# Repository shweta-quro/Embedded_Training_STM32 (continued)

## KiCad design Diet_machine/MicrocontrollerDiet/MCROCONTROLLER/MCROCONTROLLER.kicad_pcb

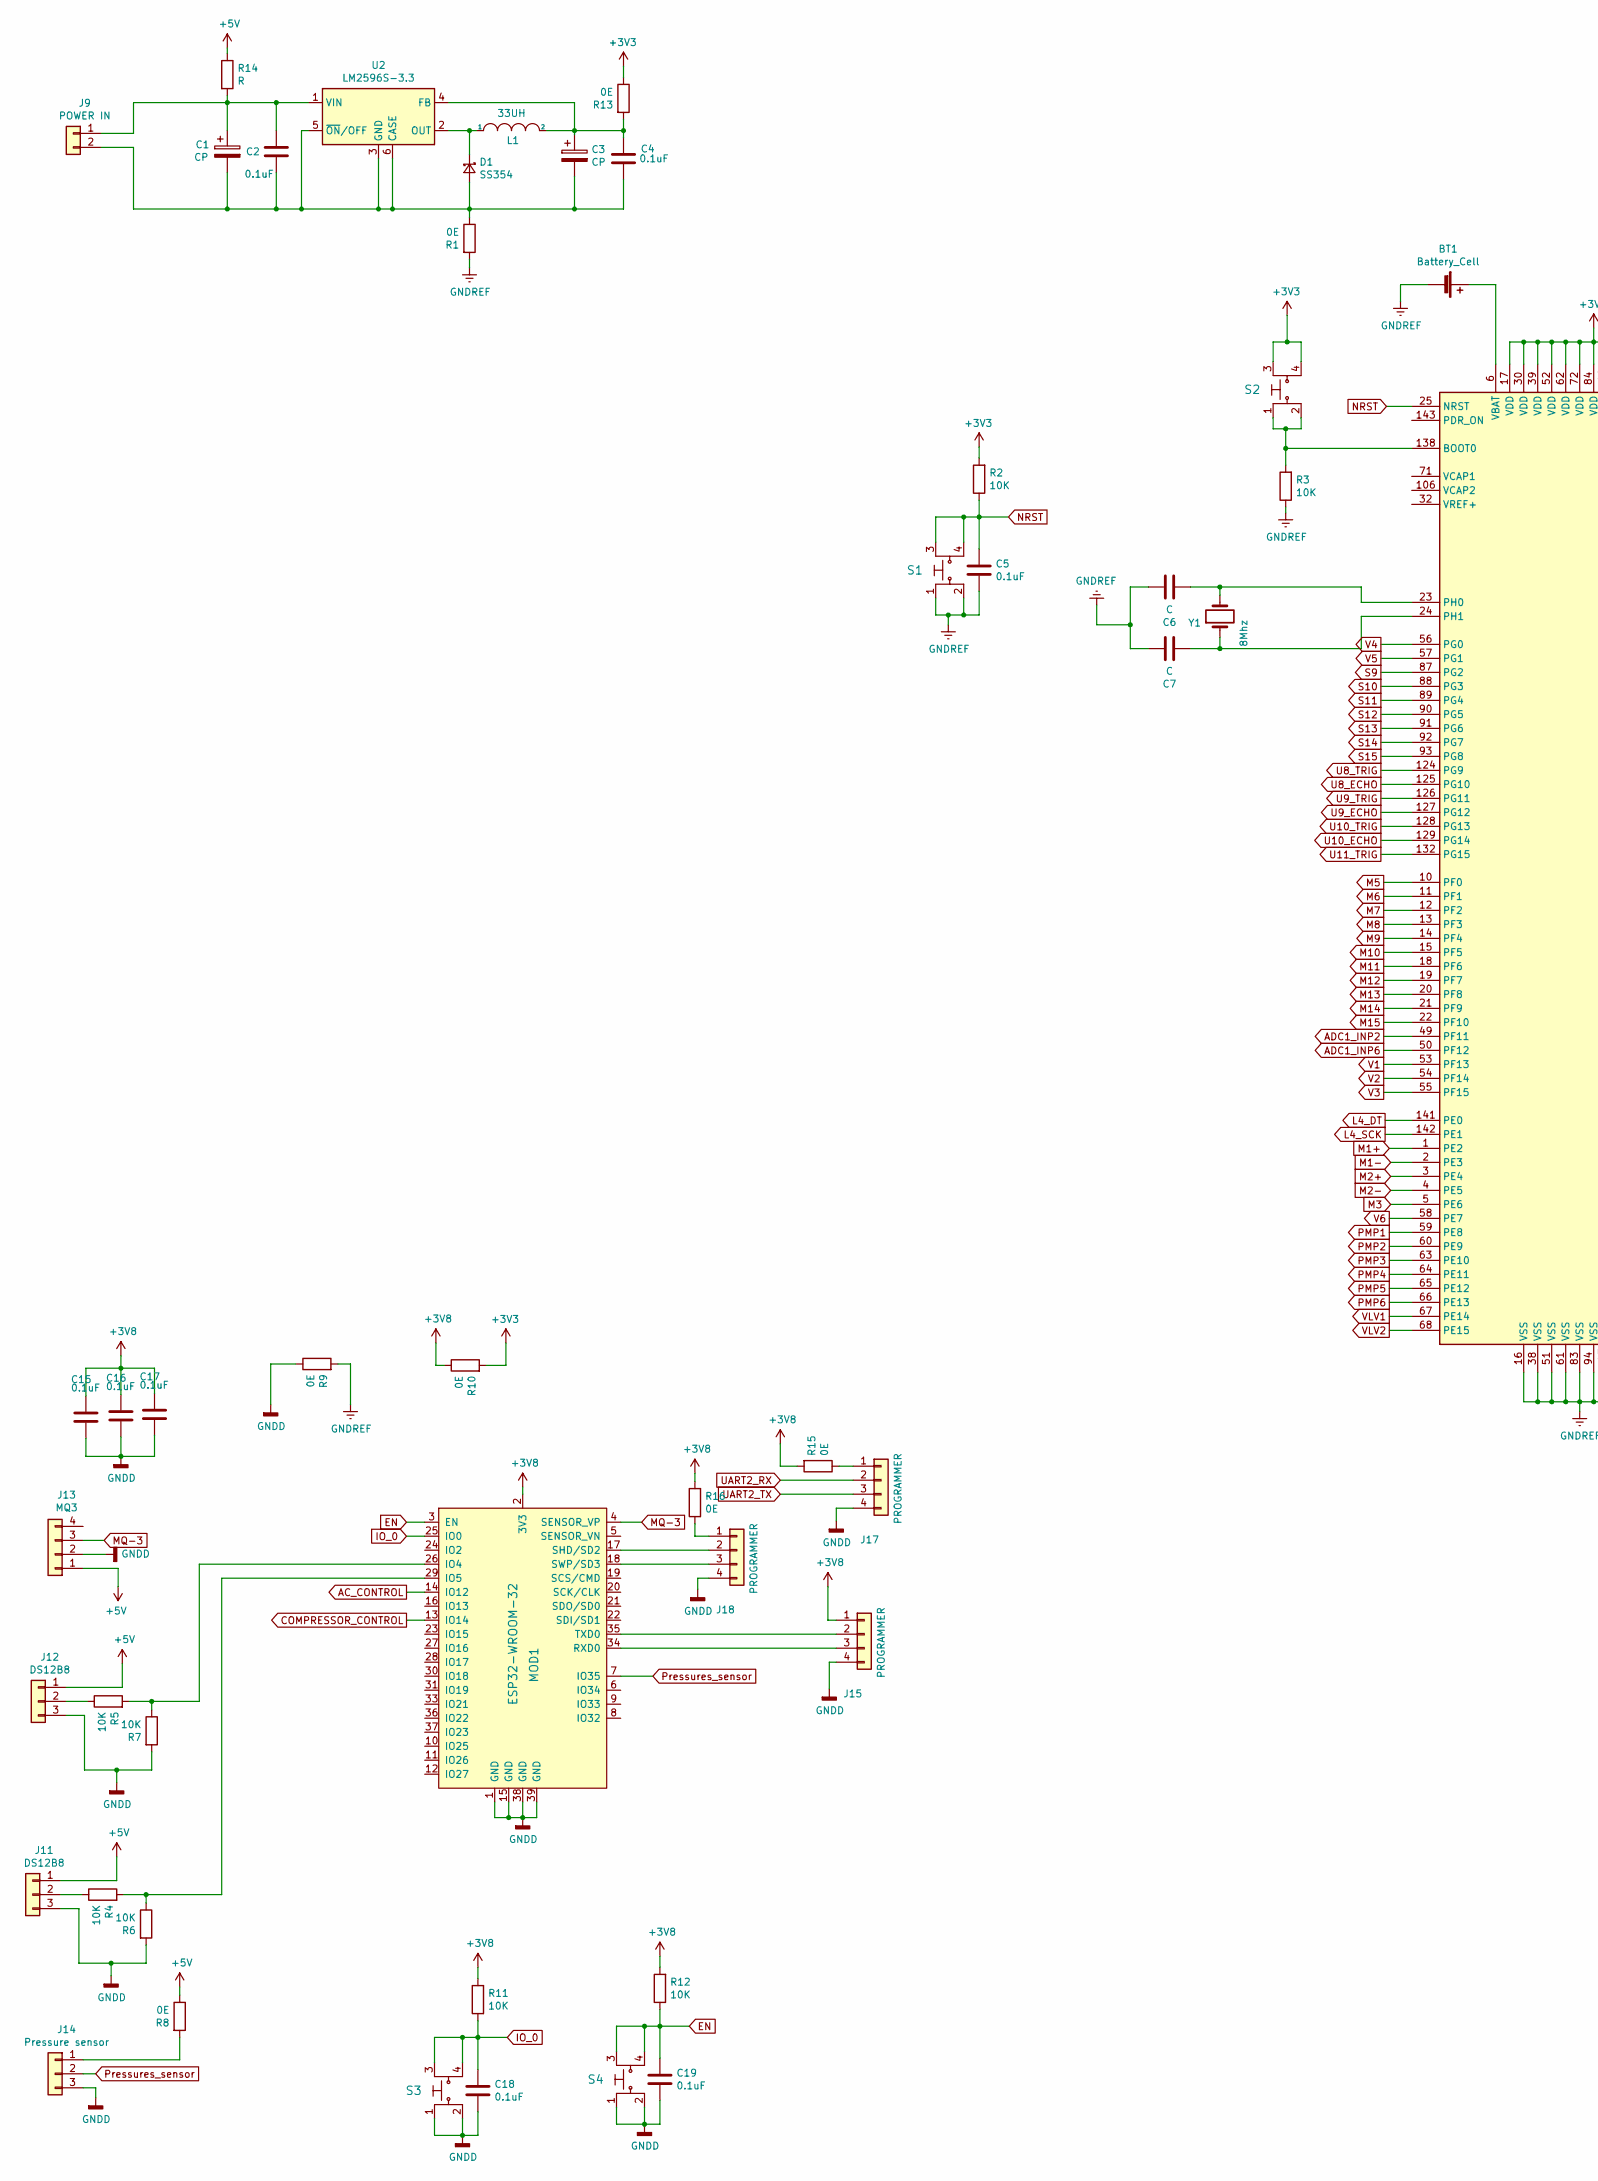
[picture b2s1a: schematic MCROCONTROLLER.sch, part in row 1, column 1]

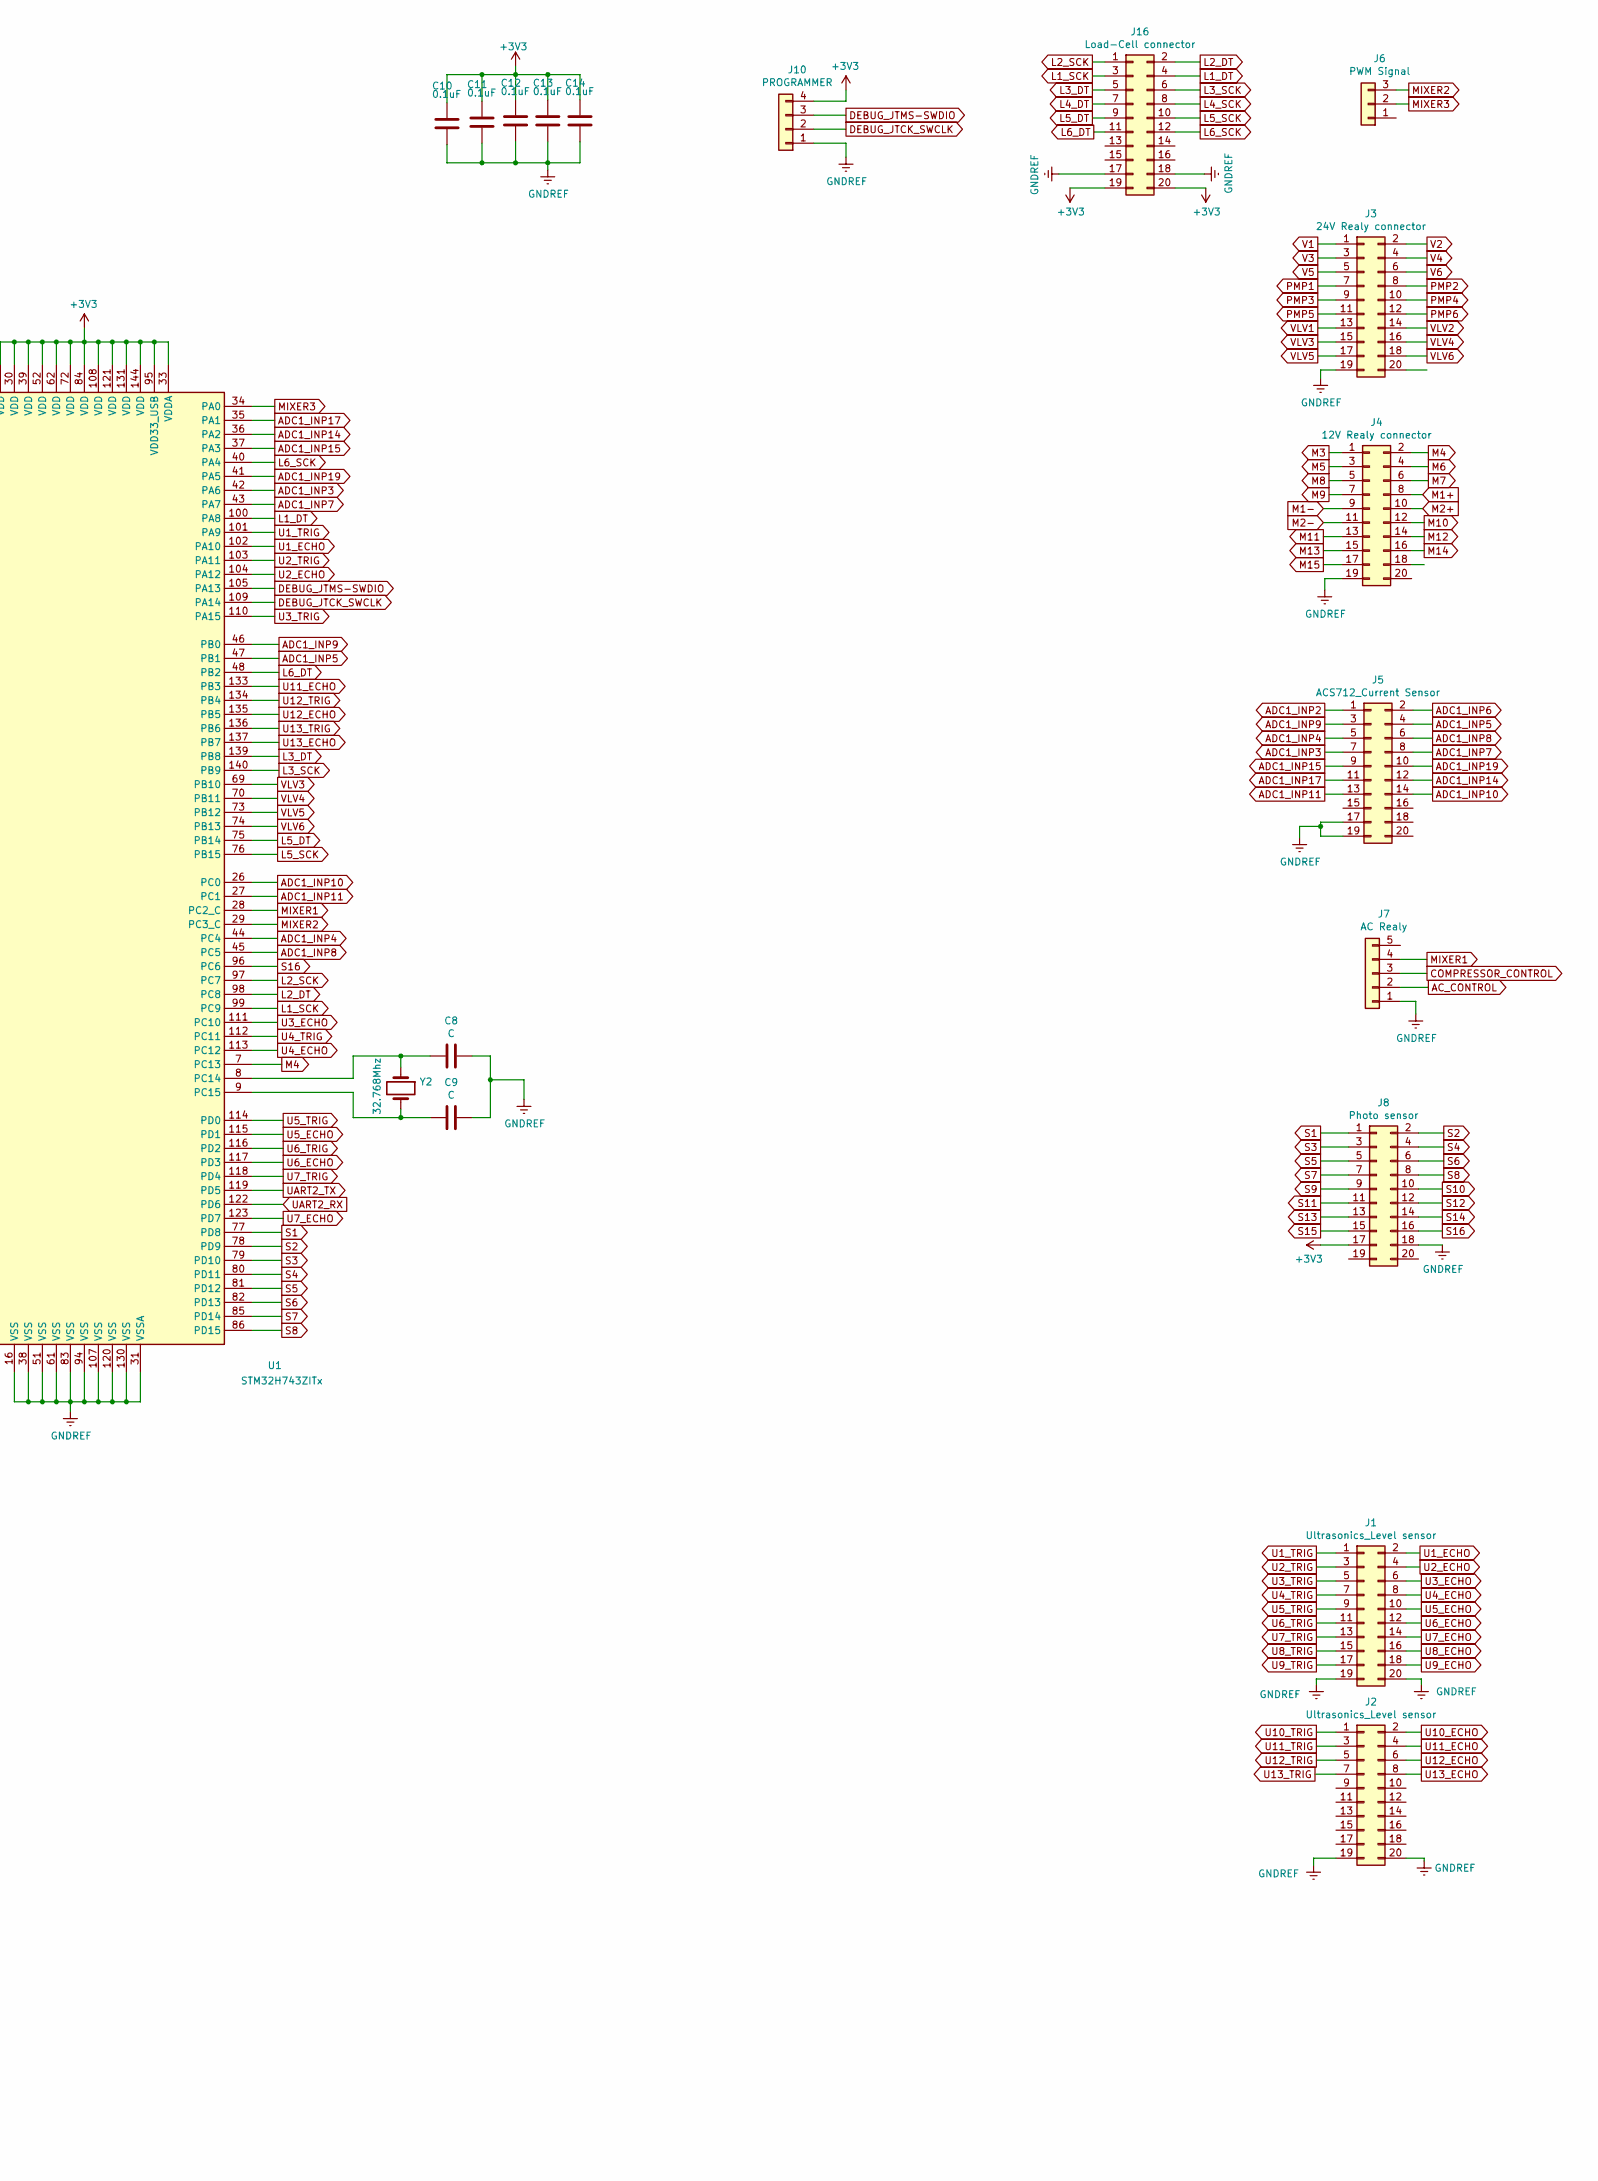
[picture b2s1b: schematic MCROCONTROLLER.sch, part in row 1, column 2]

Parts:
BT1: Battery_Cell; BatteryHolder_ComfortableElectronic_CH273-2450_1x2450
C1, C3: CP; CP_Radial_D8.0mm_P5.00mm
C2, C4, C10, C11, C12, C13, C14, C15, C16, C17: 0.1uF; C_0805_2012Metric_Pad1.18x1.45mm_HandSolder
C5, C18, C19: 0.1uF; C_0603_1608Metric
C6, C7, C8, C9: C; C_0603_1608Metric
D1: SS354; D_SS14
J1, J2: Ultrasonics_Level sensor; IDC-Header_2x10_P2.54mm_Vertical
J3: 24V Realy connector; IDC-Header_2x10_P2.54mm_Vertical
J4: 12V Realy connector; IDC-Header_2x10_P2.54mm_Vertical
J5: ACS712_Current Sensor; IDC-Header_2x10_P2.54mm_Vertical
J6: PWM Signal; PhoenixContact_MCV_1,5_3-G-5.08_1x03_P5.08mm_Vertical
J7: AC Realy; PhoenixContact_MCV_1,5_5-G-5.08_1x05_P5.08mm_Vertical
J8: Photo sensor; IDC-Header_2x10_P2.54mm_Vertical
J9: POWER IN; PhoenixContact_MCV_1,5_2-GF-5.08_1x02_P5.08mm_Vertical_Thre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
J10, J17, J18: PROGRAMMER; PinSocket_1x04_P2.54mm_Vertical
J11, J12: DS12B8; Molex_KK-254_AE-6410-03A_1x03_P2.54mm_Vertical
J13: MQ3; Molex_KK-254_AE-6410-04A_1x04_P2.54mm_Vertical
J14: Pressure sensor; Molex_KK-254_AE-6410-03A_1x03_P2.54mm_Vertical
J15: PROGRAMMER; PinSocket_2x02_P2.54mm_Vertical
J16: Load-Cell connector; IDC-Header_2x10_P2.54mm_Vertical
L1: 33UH; L_SMD1
MOD1: ESP32-WROOM-32; ESP32-WROOM-32D; MPN ESP32-WROOM-32; Digi-Key_PN 1904-1010-1-ND
R1, R9, R10, R13, R15, R16: 0E; R_1206_3216Metric
R2, R3, R4, R5, R6, R7, R11, R12: 10K; R_0603_1608Metric
R8: 0E; R_0603_1608Metric
R14: R; R_Axial_DIN0411_L9.9mm_D3.6mm_P20.32mm_Horizontal
S1, S2, S3, S4: PTS645SM43SMTR92_LFS; Switch_Tactile_THT_6x6mm; MPN PTS645SM43SMTR92 LFS; Digi-Key_PN CKN9112CT-ND
U1: STM32H743ZITx; LQFP-144_20x20mm_P0.5mm
U2: LM2596S-3.3; TO-263-5_TabPin3
Y1: 8Mhz; Crystal_HC49-4H_Vertical
Y2: 32.768Mhz; Crystal_Round_D1.5mm_Vertical

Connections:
+3V3: C10.1, C11.1, C12.1, C13.1, C14.1, J8.17, J10.4, J16.19, J16.20, R2.2, R10.2, R13.1, S2.3, S2.4, U1.17 (VDD), U1.30 (VDD), U1.33 (VDDA), U1.39 (VDD), U1.52 (VDD), U1.62 (VDD), U1.72 (VDD), U1.84 (VDD), U1.95 (VDD33_USB), U1.108 (VDD), U1.121 (VDD), U1.131 (VDD), U1.144 (VDD)
+3V8: C15.1, C16.1, C17.1, J15.1, MOD1.2 (3V3), R10.1, R11.2, R12.2, R15.2, R16.2
+5V: J11.1, J12.1, J13.1, R8.1, R14.1
AC_CONTROL: J7.2, MOD1.14 (IO12)
ADC1_INP2: J5.1, U1.49 (PF11)
ADC1_INP3: J5.7, U1.42 (PA6)
ADC1_INP4: J5.5, U1.44 (PC4)
ADC1_INP5: J5.4, U1.47 (PB1)
ADC1_INP6: J5.2, U1.50 (PF12)
ADC1_INP7: J5.8, U1.43 (PA7)
ADC1_INP8: J5.6, U1.45 (PC5)
ADC1_INP9: J5.3, U1.46 (PB0)
ADC1_INP10: J5.14, U1.26 (PC0)
ADC1_INP11: J5.13, U1.27 (PC1)
ADC1_INP14: J5.12, U1.36 (PA2)
ADC1_INP15: J5.9, U1.37 (PA3)
ADC1_INP17: J5.11, U1.35 (PA1)
ADC1_INP19: J5.10, U1.41 (PA5)
COMPRESSOR_CONTROL: J7.3, MOD1.13 (IO14)
DEBUG_JTCK_SWCLK: J10.2, U1.109 (PA14)
DEBUG_JTMS-SWDIO: J10.3, U1.105 (PA13)
EN: C19.1, MOD1.3 (EN), R12.1, S4.3, S4.4
GNDD: C15.2, C16.2, C17.2, C18.2, C19.2, J11.3, J12.3, J13.2, J14.3, J15.4, J17.4, J18.4, MOD1.1 (GND), MOD1.15 (GND), MOD1.38 (GND), MOD1.39 (GND), R6.2, R7.2, R9.1, S3.1, S3.2, S4.1, S4.2
GNDREF: BT1.2 (-), C5.2, C6.2, C7.2, C8.2, C9.2, C10.2, C11.2, C12.2, C13.2, C14.2, J1.19, J1.20, J2.19, J2.20, J3.19, J4.19, J5.17, J5.19, J7.1, J8.18, J10.1, J16.17, J16.18, R1.2, R3.1, R9.2, S1.1, S1.2, U1.16 (VSS), U1.31 (VSSA), U1.38 (VSS), U1.51 (VSS), U1.61 (VSS), U1.83 (VSS), U1.94 (VSS), U1.107 (VSS), U1.120 (VSS), U1.130 (VSS)
IO_0: C18.1, MOD1.25 (IO0), R11.1, S3.3, S3.4
L1_DT: J16.4, U1.100 (PA8)
L1_SCK: J16.3, U1.99 (PC9)
L2_DT: J16.2, U1.98 (PC8)
L2_SCK: J16.1, U1.97 (PC7)
L3_DT: J16.5, U1.139 (PB8)
L3_SCK: J16.6, U1.140 (PB9)
L4_DT: J16.7, U1.141 (PE0)
L4_SCK: J16.8, U1.142 (PE1)
L5_DT: J16.9, U1.75 (PB14)
L5_SCK: J16.10, U1.76 (PB15)
L6_DT: J16.11, U1.48 (PB2)
L6_SCK: J16.12, U1.40 (PA4)
M1+: J4.8, U1.1 (PE2)
M1-: J4.9, U1.2 (PE3)
M2+: J4.10, U1.3 (PE4)
M2-: J4.11, U1.4 (PE5)
M3: J4.1, U1.5 (PE6)
M4: J4.2, U1.7 (PC13)
M5: J4.3, U1.10 (PF0)
M6: J4.4, U1.11 (PF1)
M7: J4.6, U1.12 (PF2)
M8: J4.5, U1.13 (PF3)
M9: J4.7, U1.14 (PF4)
M10: J4.12, U1.15 (PF5)
M11: J4.13, U1.18 (PF6)
M12: J4.14, U1.19 (PF7)
M13: J4.15, U1.20 (PF8)
M14: J4.16, U1.21 (PF9)
M15: J4.17, U1.22 (PF10)
MIXER1: J7.4, U1.28 (PC2_C)
MIXER2: J6.3, U1.29 (PC3_C)
MIXER3: J6.2, U1.34 (PA0)
MQ-3: J13.3, MOD1.4 (SENSOR_VP)
NRST: C5.1, R2.1, S1.3, S1.4, U1.25 (NRST)
unnamed: BT1.1 (+), U1.6 (VBAT)
unnamed: C1.1, C2.1, J9.1, R14.2, U2.1 (VIN)
unnamed: C1.2, C2.2, C3.2, C4.2, D1.1 (A), J9.2, R1.1, U2.3 (GND), U2.5 (~ON~/OFF), U2.6 (CASE)
unnamed: C3.1, C4.1, L1.2, R13.2, U2.4 (FB)
unnamed: C6.1, U1.23 (PH0), Y1.2
unnamed: C7.1, U1.24 (PH1), Y1.1
unnamed: C8.1, U1.8 (PC14), Y2.1
unnamed: C9.1, U1.9 (PC15), Y2.2
unnamed: D1.2 (K), L1.1, U2.2 (OUT)
unnamed: J11.2, R4.1
unnamed: J12.2, R5.1
unnamed: J14.1, R8.2
unnamed: J15.2, MOD1.35 (TXD0)
unnamed: J15.3, MOD1.34 (RXD0)
unnamed: J17.1, R15.1
unnamed: J18.1, R16.1
unnamed: J18.2, MOD1.17 (SHD/SD2)
unnamed: J18.3, MOD1.18 (SWP/SD3)
unnamed: MOD1.26 (IO4), R5.2, R7.1
unnamed: MOD1.29 (IO5), R4.2, R6.1
unnamed: R3.2, S2.1, S2.2, U1.138 (BOOT0)
PMP1: J3.7, U1.59 (PE8)
PMP2: J3.8, U1.60 (PE9)
PMP3: J3.9, U1.63 (PE10)
PMP4: J3.10, U1.64 (PE11)
PMP5: J3.11, U1.65 (PE12)
PMP6: J3.12, U1.66 (PE13)
Pressures_sensor: J14.2, MOD1.7 (IO35)
S1: J8.1, U1.77 (PD8)
S2: J8.2, U1.78 (PD9)
S3: J8.3, U1.79 (PD10)
S4: J8.4, U1.80 (PD11)
S5: J8.5, U1.81 (PD12)
S6: J8.6, U1.82 (PD13)
S7: J8.7, U1.85 (PD14)
S8: J8.8, U1.86 (PD15)
S9: J8.9, U1.87 (PG2)
S10: J8.10, U1.88 (PG3)
S11: J8.11, U1.89 (PG4)
S12: J8.12, U1.90 (PG5)
S13: J8.13, U1.91 (PG6)
S14: J8.14, U1.92 (PG7)
S15: J8.15, U1.93 (PG8)
S16: J8.16, U1.96 (PC6)
U1_ECHO: J1.2, U1.102 (PA10)
U1_TRIG: J1.1, U1.101 (PA9)
U2_ECHO: J1.4, U1.104 (PA12)
U2_TRIG: J1.3, U1.103 (PA11)
U3_ECHO: J1.6, U1.111 (PC10)
U3_TRIG: J1.5, U1.110 (PA15)
U4_ECHO: J1.8, U1.113 (PC12)
U4_TRIG: J1.7, U1.112 (PC11)
U5_ECHO: J1.10, U1.115 (PD1)
U5_TRIG: J1.9, U1.114 (PD0)
U6_ECHO: J1.12, U1.117 (PD3)
U6_TRIG: J1.11, U1.116 (PD2)
U7_ECHO: J1.14, U1.123 (PD7)
U7_TRIG: J1.13, U1.118 (PD4)
U8_ECHO: J1.16, U1.125 (PG10)
U8_TRIG: J1.15, U1.124 (PG9)
U9_ECHO: J1.18, U1.127 (PG12)
U9_TRIG: J1.17, U1.126 (PG11)
U10_ECHO: J2.2, U1.129 (PG14)
U10_TRIG: J2.1, U1.128 (PG13)
U11_ECHO: J2.4, U1.133 (PB3)
U11_TRIG: J2.3, U1.132 (PG15)
U12_ECHO: J2.6, U1.135 (PB5)
U12_TRIG: J2.5, U1.134 (PB4)
U13_ECHO: J2.8, U1.137 (PB7)
U13_TRIG: J2.7, U1.136 (PB6)
UART2_RX: J17.2, U1.122 (PD6)
UART2_TX: J17.3, U1.119 (PD5)
V1: J3.1, U1.53 (PF13)
V2: J3.2, U1.54 (PF14)
V3: J3.3, U1.55 (PF15)
V4: J3.4, U1.56 (PG0)
V5: J3.5, U1.57 (PG1)
V6: J3.6, U1.58 (PE7)
VLV1: J3.13, U1.67 (PE14)
VLV2: J3.14, U1.68 (PE15)
VLV3: J3.15, U1.69 (PB10)
VLV4: J3.16, U1.70 (PB11)
VLV5: J3.17, U1.73 (PB12)
VLV6: J3.18, U1.74 (PB13)

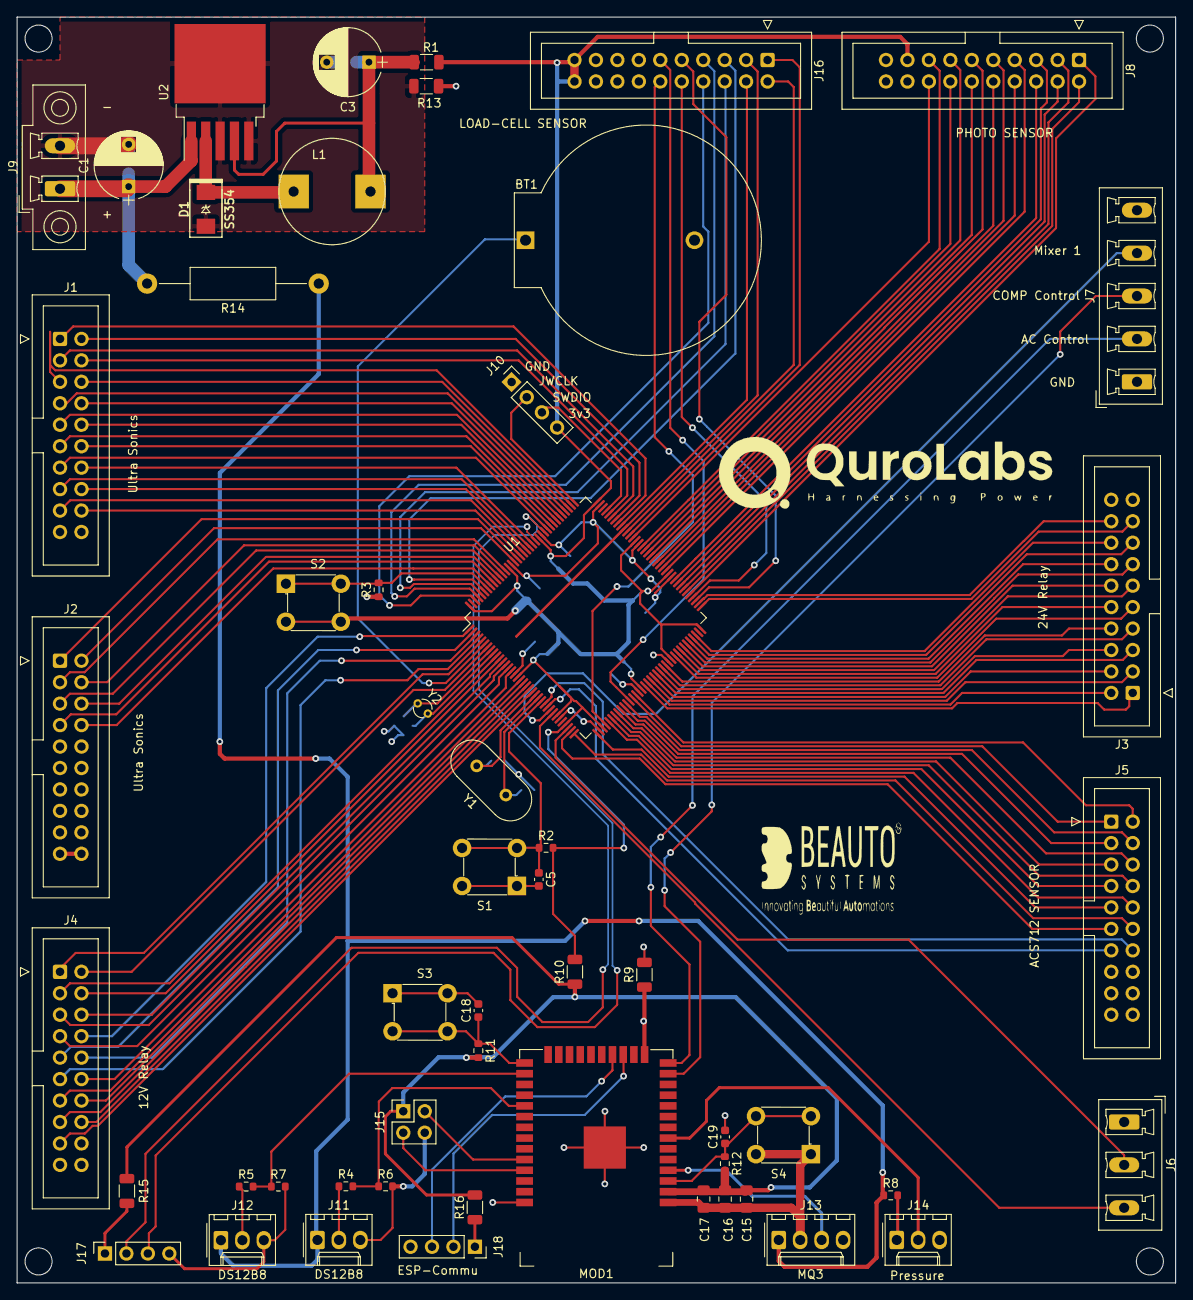
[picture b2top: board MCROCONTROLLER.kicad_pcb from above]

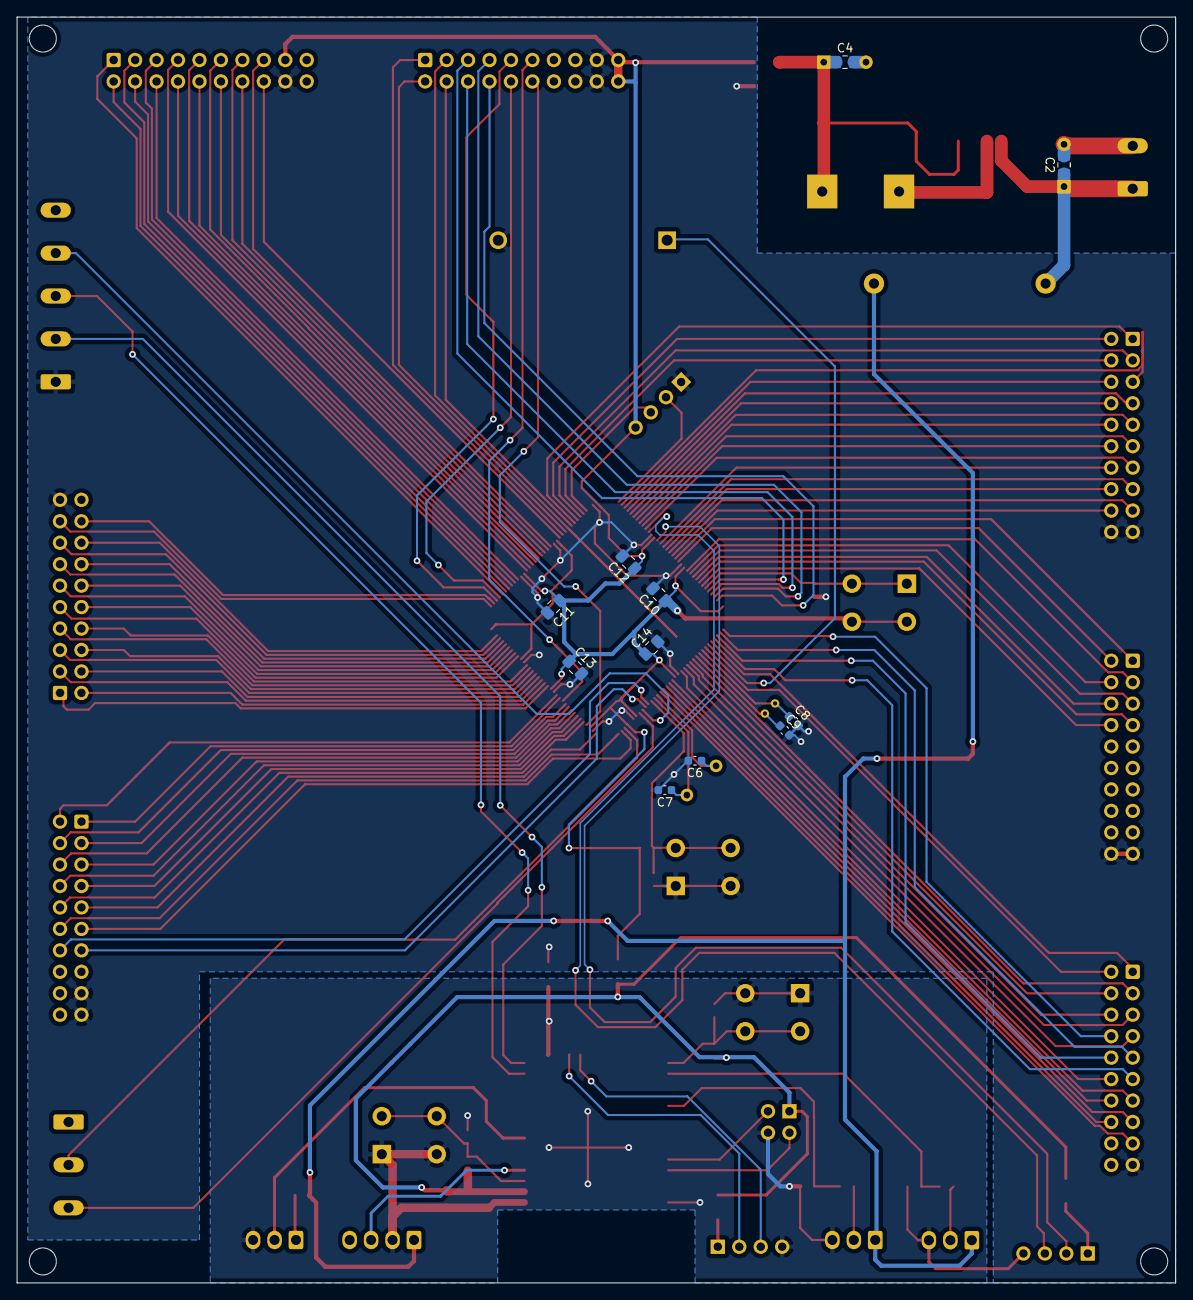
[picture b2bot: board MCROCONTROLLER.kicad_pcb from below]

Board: 2 copper layers, 137.2 x 149.9 mm, 65 parts (11 on the bottom side), 143 nets.

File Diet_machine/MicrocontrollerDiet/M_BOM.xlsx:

Sr. No | Sourced | Placed | References | Value | Footprint | Quantity
1 |  |  | C2, C4, C10, C11, C12, C13, C14, C15, C16, C17 | 0.1uF | C_0805_2012Metric_Pad1.18x1.45mm_HandSolder | 10
2 |  |  | C6, C7, C8, C9 | C | C_0603_1608Metric | 4
3 |  |  | C5, C18, C19 | 0.1uF | C_0603_1608Metric | 3
4 |  |  | C1, C3 | CP | CP_Radial_D8.0mm_P5.00mm | 2
5 |  |  | R2, R3, R4, R5, R6, R7, R11, R12 | 10K | R_0603_1608Metric | 8
6 |  |  | R1, R9, R10, R13, R15, R16 | 0E | R_1206_3216Metric | 6
7 |  |  | R8 | 0E | R_0603_1608Metric | 1
8 |  |  | R14 | R | R_Axial_DIN0411_L9.9mm_D3.6mm_P20.32mm_Horizontal | 1
9 |  |  | L1 | 33UH | L_SMD1 | 1
10 |  |  | D1 | SS354 | D_SS14 | 1
11 |  |  | U1 | STM32H743ZITx | LQFP-144_20x20mm_P0.5mm | 1
12 | inHOUSE |  | U2 | LM2596S-3.3 | TO-263-5_TabPin3 | 1
13 | inHOUSE |  | Y1 | 8Mhz | Crystal_HC49-4H_Vertical | 1
14 | inHOUSE |  | Y2 | 32.768Mhz | Crystal_Round_D1.5mm_Vertical | 1
15 |  |  | S1, S2, S3, S4 | PTS645SM43SMTR92_LFS | Switch_Tactile_THT_6x6mm | 4
16 |  |  | BT1 | Battery_Cell | BatteryHolder_ComfortableElectronic_CH273-2450_1x2450 | 1
19 | inHOUSE |  | MOD1 | ESP32-WROOM-32 | ESP32-WROOM-32D | 1
20 |  |  | J1, J2 | Ultrasonics_Level sensor | IDC-Header_2x10_P2.54mm_Vertical | 2
21 |  |  | J10, J17 | PROGRAMMER | PinSocket_1x04_P2.54mm_Vertical | 2
22 |  |  | J11, J12 | DS12B8 | Molex_KK-254_AE-6410-03A_1x03_P2.54mm_Vertical | 2
23 |  |  | J3 | 24V Realy connector | IDC-Header_2x10_P2.54mm_Vertical | 1
24 |  |  | J4 | 12V Realy connector | IDC-Header_2x10_P2.54mm_Vertical | 1
25 |  |  | J5 | ACS712_Current Sensor | IDC-Header_2x10_P2.54mm_Vertical | 1
26 |  |  | J6 | PWM Signal | PhoenixContact_MCV_1,5_3-G-5.08_1x03_P5.08mm_Vertical | 1
27 |  |  | J7 | AC Realy | PhoenixContact_MCV_1,5_5-G-5.08_1x05_P5.08mm_Vertical | 1
28 |  |  | J8 | Photo sensor | IDC-Header_2x10_P2.54mm_Vertical | 1
29 |  |  | J9 | POWER IN | PhoenixContact_MCV_1,5_2-GF-5.08_1x02_P5.08mm_Vertical_ThreadedFlange | 1
30 |  |  | J13 | MQ3 | Molex_KK-254_AE-6410-04A_1x04_P2.54mm_Vertical | 1
31 |  |  | J14 | Pressure sensor | Molex_KK-254_AE-6410-03A_1x03_P2.54mm_Vertical | 1
32 |  |  | J15 | PROGRAMMER | PinSocket_2x02_P2.54mm_Vertical | 1
33 |  |  | J16 | Load-Cell connector | IDC-Header_2x10_P2.54mm_Vertical | 1
34 |  |  | J18 | ESP-32 Comm | PinSocket_1x04_P2.54mm_Vertical | 1

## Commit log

2022-08-26 Create STM32_Blinking_LED
2022-09-12 SlaveId Program upload
2022-09-12 project upload
